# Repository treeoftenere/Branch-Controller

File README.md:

# Branch-Controller

The branch controllers are running on STM32 Bluepill boards with a wiznet w5500 based ethernet module.

The branch controller depends on the following:
1. Arduino support for STM32F1  ** master? **
2. FastLED with support for STM32F1  ** Currently uses Tenere Branch **
3. Ethernet library, based on the teensy implementation with faster settings  ** master? **

## Arduino settings:
Board:  Generic STM32F103C
Upload Method:  JLink

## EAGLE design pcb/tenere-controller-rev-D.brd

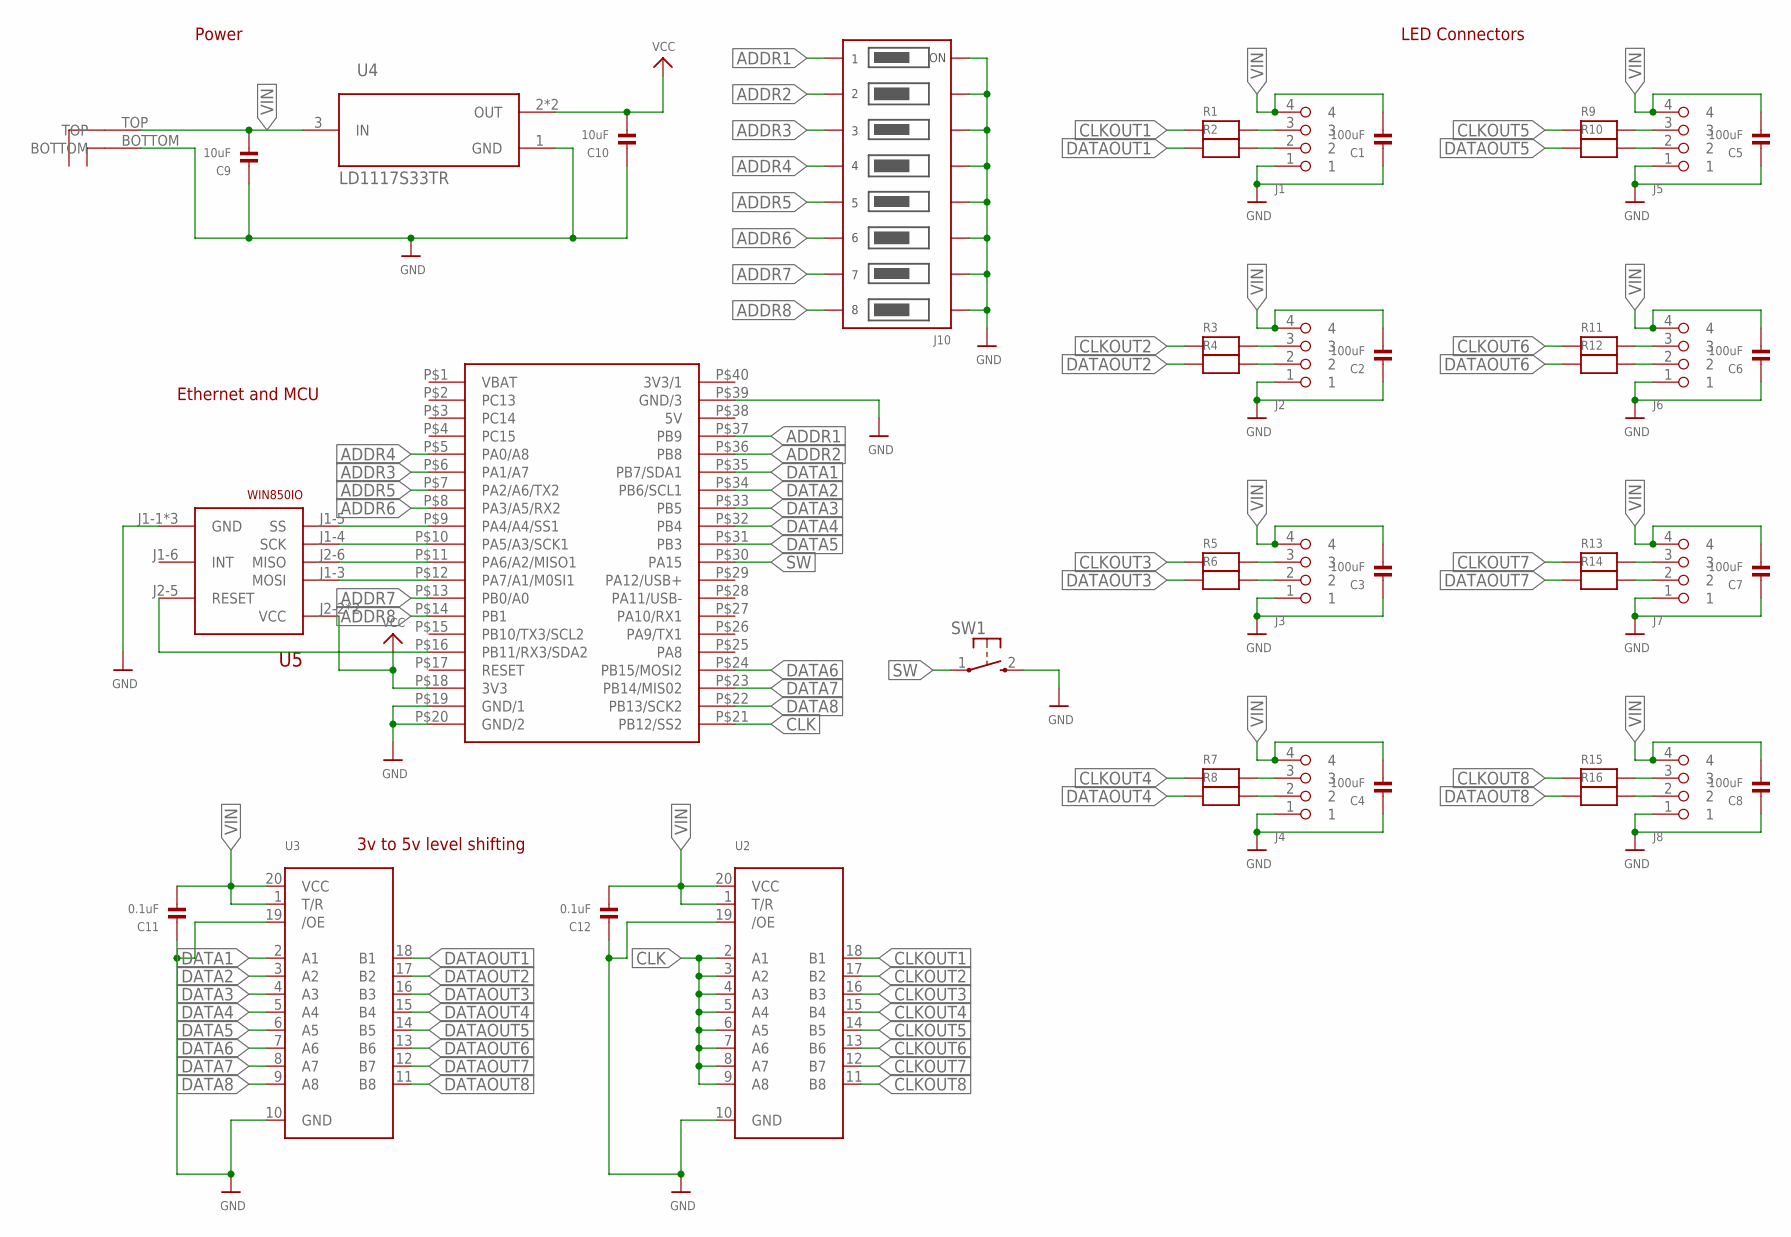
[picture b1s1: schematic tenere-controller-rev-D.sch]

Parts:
C1, C2, C3, C4, C5, C6, C7, C8: 100uF; 1206
C9, C10: 10uF; 0603
C11, C12: 0.1uF; 0603
J1, J2, J3, J4, J5, J6, J7, J8: MICROFIT3; 43650-0400
J9: POWERPOLE-2V; POWERPOLE_STACKED
J10: DIP-SWITCH-8PIN; BPA08B
R1, R2, R3, R4, R5, R6, R7, R8, R9, R10, R11, R12, R13, R14, R15, R16: RESISTOR0603; 0603
SW1: TACTILE-SWITCH-1825027; 1825027
U1: BLUEPILL; 40-DIP-BLUE-PIL
U2, U3: 74LCX245; TSSOP20
U4: LD1117S33TR; LD1117S33TR_SOT230P700X180-4N
U5: WIN850IO; WIZ850IO

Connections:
ADDR1: J10.1' (1B), U1.P$37 (PB9)
ADDR2: J10.2' (2B), U1.P$36 (PB8)
ADDR3: J10.3' (3B), U1.P$6 (PA1/A7)
ADDR4: J10.4' (4B), U1.P$5 (PA0/A8)
ADDR5: J10.5' (5B), U1.P$7 (PA2/A6/TX2)
ADDR6: J10.6' (6B), U1.P$8 (PA3/A5/RX2)
ADDR7: J10.7' (7B), U1.P$13 (PB0/A0)
ADDR8: J10.8' (8B), U1.P$14 (PB1)
CLK: U1.P$21 (PB12/SS2), U2.2 (A1), U2.3 (A2), U2.4 (A3), U2.5 (A4), U2.6 (A5), U2.7 (A6), U2.8 (A7), U2.9 (A8)
CLKOUT1: R1.1, U2.18 (B1)
CLKOUT2: R3.1, U2.17 (B2)
CLKOUT3: R5.1, U2.16 (B3)
CLKOUT4: R7.1, U2.15 (B4)
CLKOUT5: R9.1, U2.14 (B5)
CLKOUT6: R11.1, U2.13 (B6)
CLKOUT7: R13.1, U2.12 (B7)
CLKOUT8: R15.1, U2.11 (B8)
DATA1: U1.P$35 (PB7/SDA1), U3.2 (A1)
DATA2: U1.P$34 (PB6/SCL1), U3.3 (A2)
DATA3: U1.P$33 (PB5), U3.4 (A3)
DATA4: U1.P$32 (PB4), U3.5 (A4)
DATA5: U1.P$31 (PB3), U3.6 (A5)
DATA6: U1.P$24 (PB15/MOSI2), U3.7 (A6)
DATA7: U1.P$23 (PB14/MIS02), U3.8 (A7)
DATA8: U1.P$22 (PB13/SCK2), U3.9 (A8)
DATAOUT1: R2.1, U3.18 (B1)
DATAOUT2: R4.1, U3.17 (B2)
DATAOUT3: R6.1, U3.16 (B3)
DATAOUT4: R8.1, U3.15 (B4)
DATAOUT5: R10.1, U3.14 (B5)
DATAOUT6: R12.1, U3.13 (B6)
DATAOUT7: R14.1, U3.12 (B7)
DATAOUT8: R16.1, U3.11 (B8)
GND: C1.1, C2.1, C3.1, C4.1, C5.1, C6.1, C7.1, C8.1, C9.1, C10.1, C11.1, C12.1, J1.1, J2.1, J3.1, J4.1, J5.1, J6.1, J7.1, J8.1, J9.BOTTOM, J10.1 (1A), J10.2 (2A), J10.3 (3A), J10.4 (4A), J10.5 (5A), J10.6 (6A), J10.7 (7A), J10.8 (8A), SW1.2 (3), U1.P$19 (GND/1), U1.P$20 (GND/2), U1.P$39 (GND/3), U2.10 (GND), U2.19 (/OE), U3.10 (GND), U3.19 (/OE), U4.1 (GND), U5.J1-1 (GND), U5.J1-2 (GND), U5.J2-1 (GND)
unnamed: U1.P$9 (PA4/A4/SS1), U5.J1-5 (SS)
unnamed: U1.P$10 (PA5/A3/SCK1), U5.J1-4 (SCK)
unnamed: U1.P$11 (PA6/A2/MISO1), U5.J2-6 (MISO)
unnamed: U1.P$12 (PA7/A1/M0SI1), U5.J1-3 (MOSI)
unnamed: J1.3, R1.2
unnamed: J1.2, R2.2
unnamed: J2.3, R3.2
unnamed: J2.2, R4.2
unnamed: J3.3, R5.2
unnamed: J3.2, R6.2
unnamed: J4.3, R7.2
unnamed: J4.2, R8.2
unnamed: J5.3, R9.2
unnamed: J5.2, R10.2
unnamed: J6.3, R11.2
unnamed: J6.2, R12.2
unnamed: J7.3, R13.2
unnamed: J7.2, R14.2
unnamed: J8.3, R15.2
unnamed: J8.2, R16.2
unnamed: U1.P$16 (PB11/RX3/SDA2), U5.J2-5 (RESET)
SW: SW1.1, U1.P$30 (PA15)
VCC: C10.2, U1.P$18 (3V3), U4.2 (OUT), U4.4 (OUT), U5.J2-2 (VCC), U5.J2-3 (VCC)
VIN: C1.2, C2.2, C3.2, C4.2, C5.2, C6.2, C7.2, C8.2, C9.2, C11.2, C12.2, J1.4, J2.4, J3.4, J4.4, J5.4, J6.4, J7.4, J8.4, J9.TOP, U2.1 (T/R), U2.20 (VCC), U3.1 (T/R), U3.20 (VCC), U4.3 (IN)

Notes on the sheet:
LED Connectors
Power
Ethernet and MCU
3v to 5v level shifting

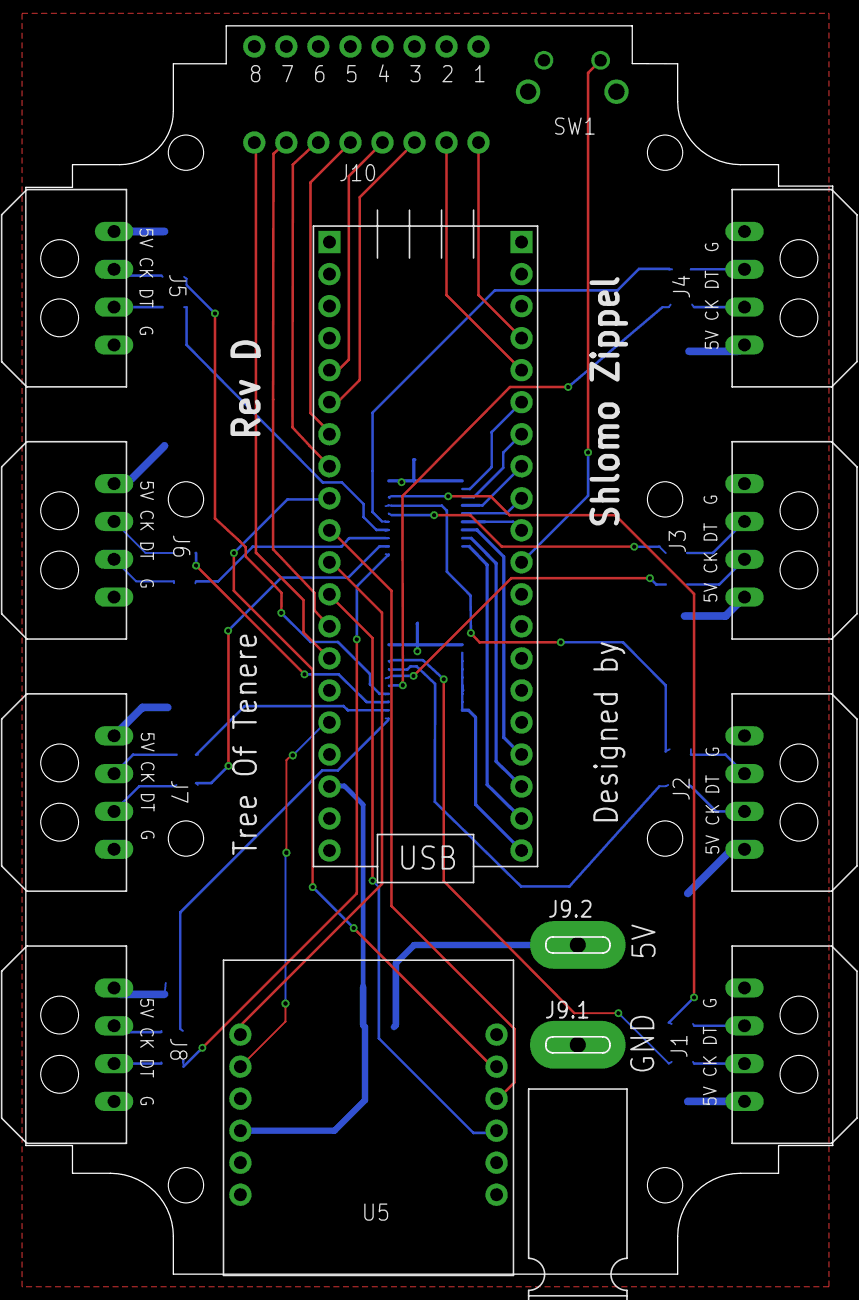
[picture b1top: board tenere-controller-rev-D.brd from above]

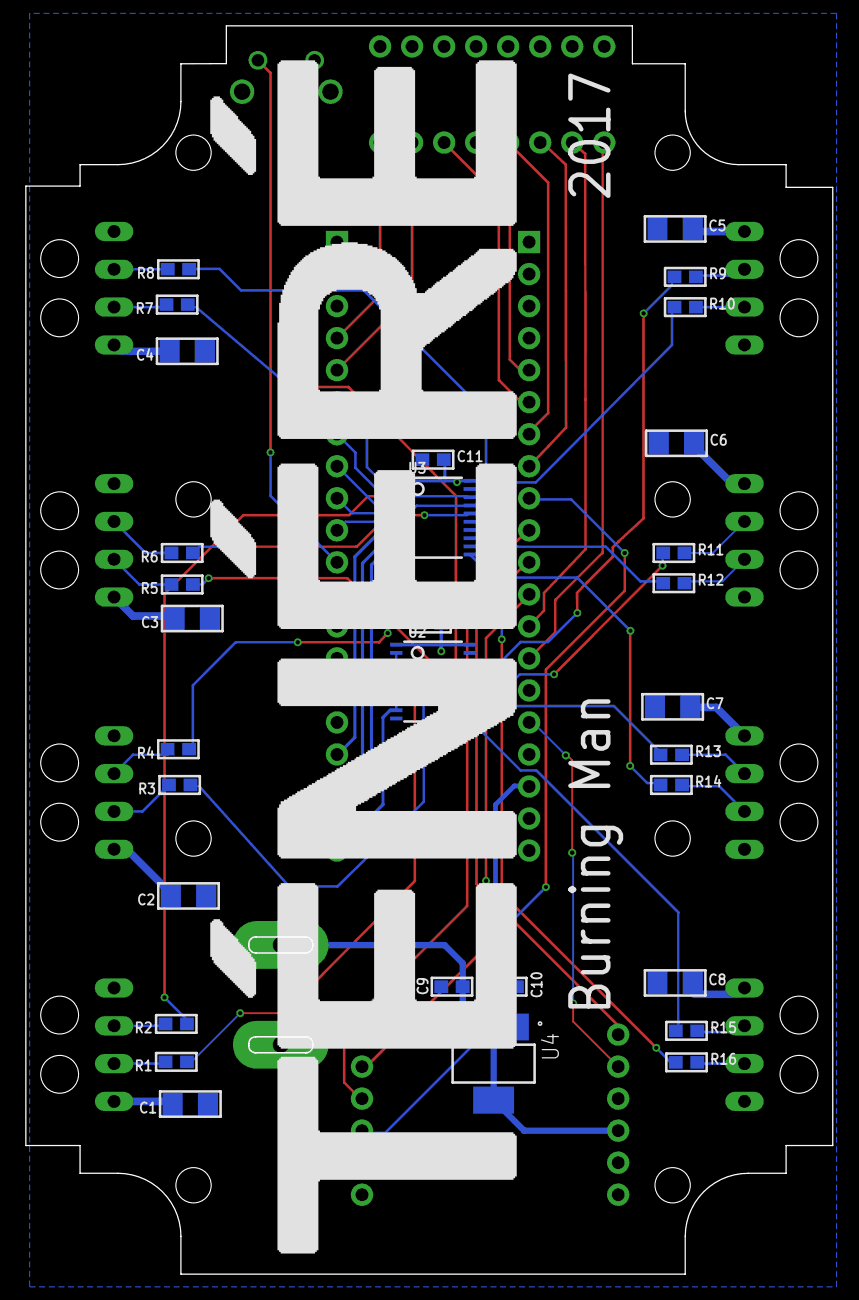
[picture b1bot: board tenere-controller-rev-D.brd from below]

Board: 2 copper layers, 64.0 x 99.0 mm, 45 parts (31 on the bottom side), 58 nets.

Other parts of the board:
U$15: 105*65

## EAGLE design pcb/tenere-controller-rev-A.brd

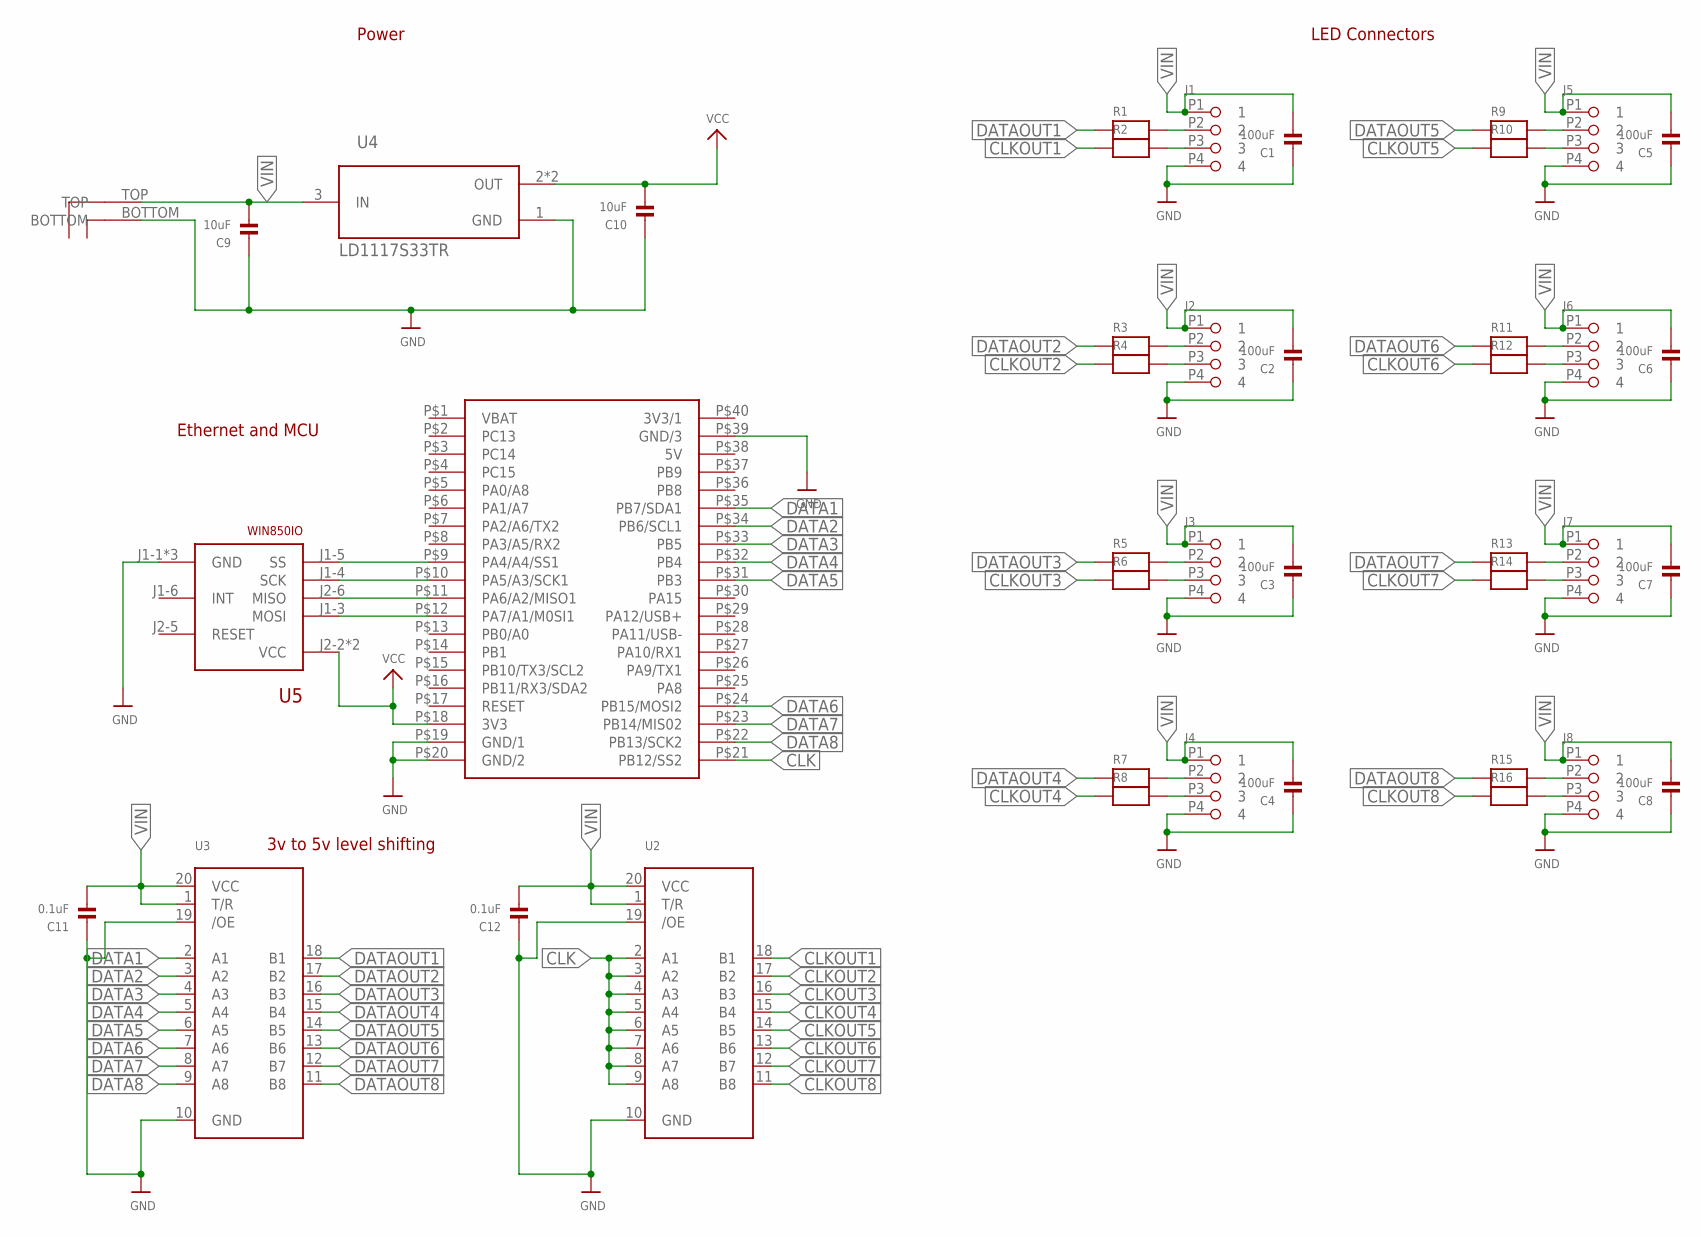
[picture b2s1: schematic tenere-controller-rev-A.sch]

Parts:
C1, C2, C3, C4, C5, C6, C7, C8: 100uF; 1206
C9, C10: 10uF; 0603
C11, C12: 0.1uF; 0603
J1, J2, J3, J4, J5, J6, J7, J8: JST-XH-4P-SODE; JST-XH-BS4P
J9: POWERPOLE-2V; POWERPOLE_STACKED
R1, R2, R3, R4, R5, R6, R7, R8, R9, R10, R11, R12, R13, R14, R15, R16: RESISTOR0603; 0603
U1: BLUEPILL; 40-DIP-BLUE-PIL
U2, U3: 74LCX245; TSSOP20
U4: LD1117S33TR; LD1117S33TR_SOT230P700X180-4N
U5: WIN850IO; WIZ850IO

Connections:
CLK: U1.P$21 (PB12/SS2), U2.2 (A1), U2.3 (A2), U2.4 (A3), U2.5 (A4), U2.6 (A5), U2.7 (A6), U2.8 (A7), U2.9 (A8)
CLKOUT1: R2.1, U2.18 (B1)
CLKOUT2: R4.1, U2.17 (B2)
CLKOUT3: R6.1, U2.16 (B3)
CLKOUT4: R8.1, U2.15 (B4)
CLKOUT5: R10.1, U2.14 (B5)
CLKOUT6: R12.1, U2.13 (B6)
CLKOUT7: R14.1, U2.12 (B7)
CLKOUT8: R16.1, U2.11 (B8)
DATA1: U1.P$35 (PB7/SDA1), U3.2 (A1)
DATA2: U1.P$34 (PB6/SCL1), U3.3 (A2)
DATA3: U1.P$33 (PB5), U3.4 (A3)
DATA4: U1.P$32 (PB4), U3.5 (A4)
DATA5: U1.P$31 (PB3), U3.6 (A5)
DATA6: U1.P$24 (PB15/MOSI2), U3.7 (A6)
DATA7: U1.P$23 (PB14/MIS02), U3.8 (A7)
DATA8: U1.P$22 (PB13/SCK2), U3.9 (A8)
DATAOUT1: R1.1, U3.18 (B1)
DATAOUT2: R3.1, U3.17 (B2)
DATAOUT3: R5.1, U3.16 (B3)
DATAOUT4: R7.1, U3.15 (B4)
DATAOUT5: R9.1, U3.14 (B5)
DATAOUT6: R11.1, U3.13 (B6)
DATAOUT7: R13.1, U3.12 (B7)
DATAOUT8: R15.1, U3.11 (B8)
GND: C1.1, C2.1, C3.1, C4.1, C5.1, C6.1, C7.1, C8.1, C9.1, C10.1, C11.1, C12.1, J1.P4 (4), J2.P4 (4), J3.P4 (4), J4.P4 (4), J5.P4 (4), J6.P4 (4), J7.P4 (4), J8.P4 (4), J9.BOTTOM, U1.P$19 (GND/1), U1.P$20 (GND/2), U1.P$39 (GND/3), U2.10 (GND), U2.19 (/OE), U3.10 (GND), U3.19 (/OE), U4.1 (GND), U5.J1-1 (GND), U5.J1-2 (GND), U5.J2-1 (GND)
unnamed: U1.P$9 (PA4/A4/SS1), U5.J1-5 (SS)
unnamed: U1.P$10 (PA5/A3/SCK1), U5.J1-4 (SCK)
unnamed: U1.P$11 (PA6/A2/MISO1), U5.J2-6 (MISO)
unnamed: U1.P$12 (PA7/A1/M0SI1), U5.J1-3 (MOSI)
unnamed: J1.P2 (2), R1.2
unnamed: J1.P3 (3), R2.2
unnamed: J2.P2 (2), R3.2
unnamed: J2.P3 (3), R4.2
unnamed: J3.P2 (2), R5.2
unnamed: J3.P3 (3), R6.2
unnamed: J4.P2 (2), R7.2
unnamed: J4.P3 (3), R8.2
unnamed: J5.P2 (2), R9.2
unnamed: J5.P3 (3), R10.2
unnamed: J6.P2 (2), R11.2
unnamed: J6.P3 (3), R12.2
unnamed: J7.P2 (2), R13.2
unnamed: J7.P3 (3), R14.2
unnamed: J8.P2 (2), R15.2
unnamed: J8.P3 (3), R16.2
VCC: C10.2, U1.P$18 (3V3), U4.2 (OUT), U4.4 (OUT), U5.J2-2 (VCC), U5.J2-3 (VCC)
VIN: C1.2, C2.2, C3.2, C4.2, C5.2, C6.2, C7.2, C8.2, C9.2, C11.2, C12.2, J1.P1 (1), J2.P1 (1), J3.P1 (1), J4.P1 (1), J5.P1 (1), J6.P1 (1), J7.P1 (1), J8.P1 (1), J9.TOP, U2.1 (T/R), U2.20 (VCC), U3.1 (T/R), U3.20 (VCC), U4.3 (IN)

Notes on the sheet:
LED Connectors
Power
Ethernet and MCU
3v to 5v level shifting

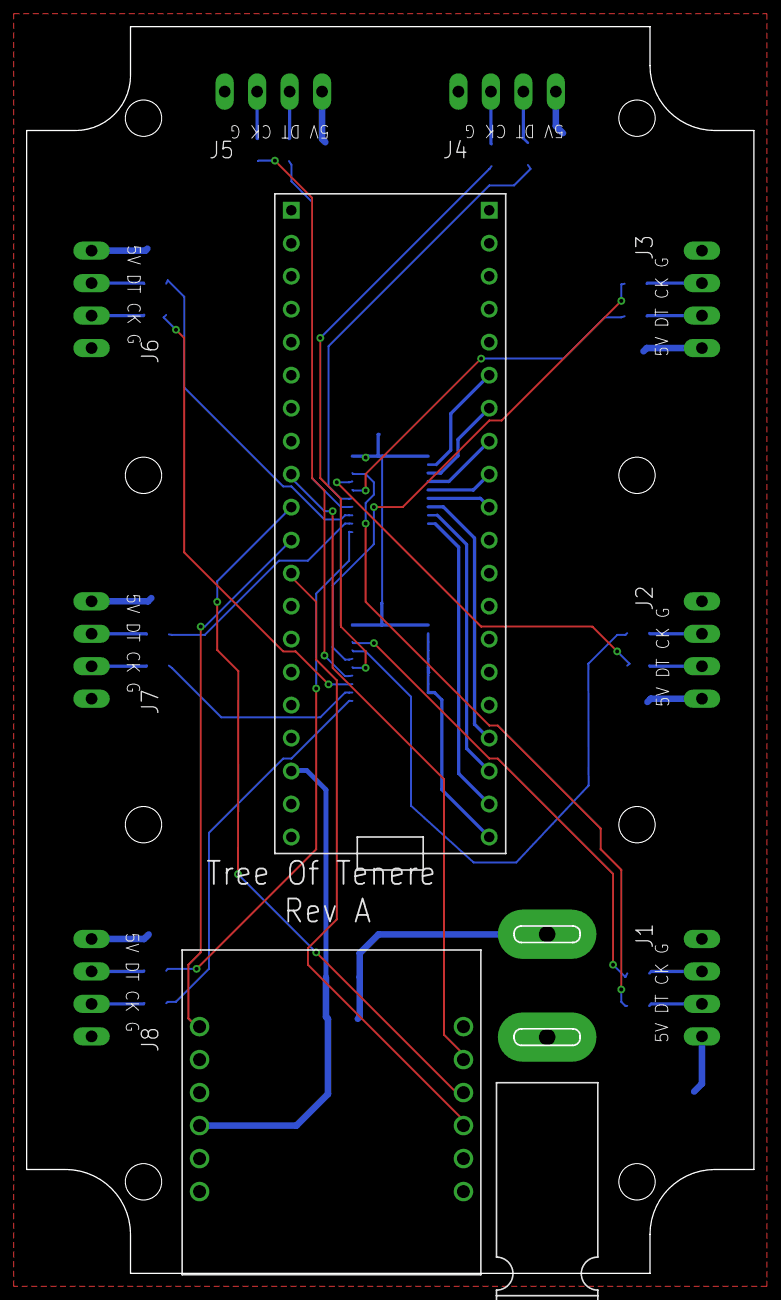
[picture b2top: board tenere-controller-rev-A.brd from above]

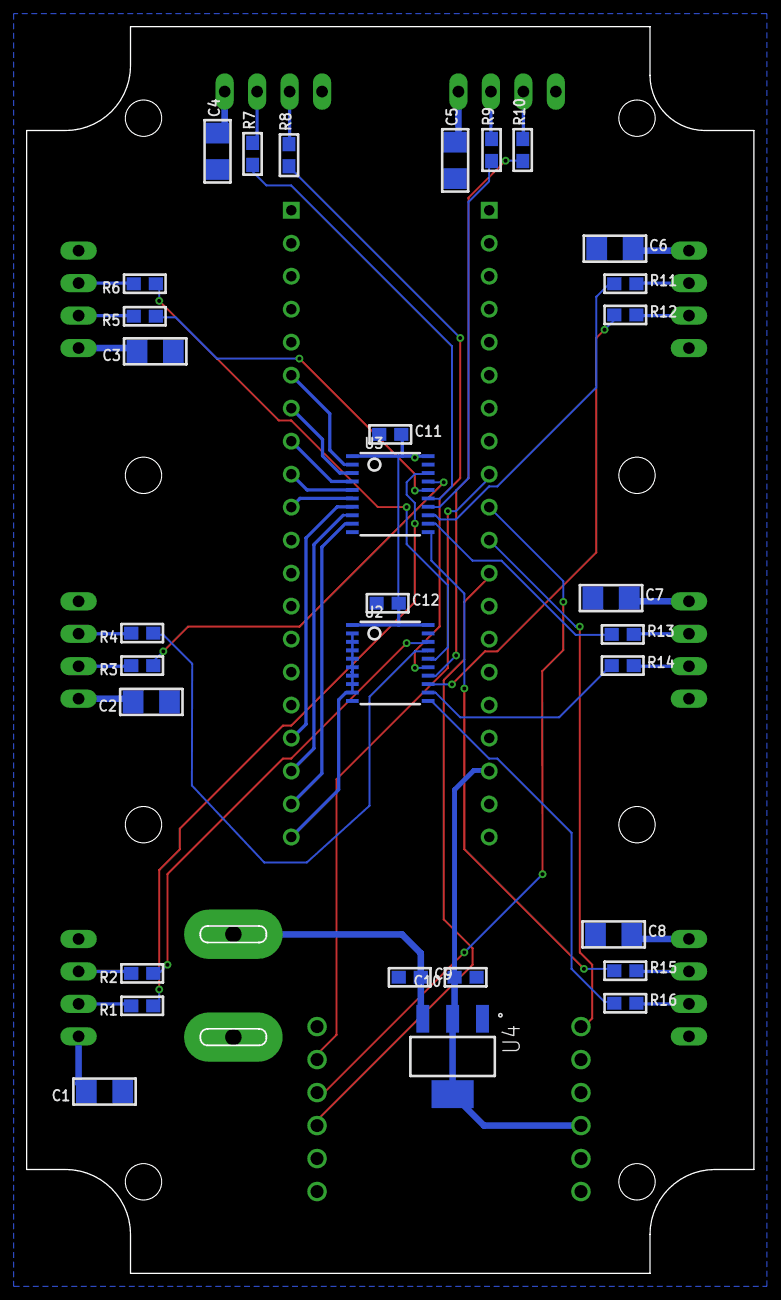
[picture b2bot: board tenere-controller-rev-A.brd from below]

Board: 2 copper layers, 56.0 x 96.0 mm, 43 parts (31 on the bottom side), 48 nets.

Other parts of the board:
U$15: 105*65

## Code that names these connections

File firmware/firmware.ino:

#include <SPI.h>
#include <Ethernet.h>
#include <FastLED.h>
#include <EEPROM.h>
#include "button.h"

#define LEDS_PER_CHANNEL    105
#define NUM_CHANNELS        8
#define NUM_LEDS            (NUM_CHANNELS * LEDS_PER_CHANNEL)
#define COLOR_ORDER         BGR
#define SPI_RATE            DATA_RATE_MHZ(4)
#define UDP_RX_BUFFER_SIZE  8192
#define UDP_PORT_NUMBER     1337

#define PARALLEL_OUTPUT
#define PLAYA_MODE

//-------------------------------------------------------------------------------------------
// Pin mappings
//-------------------------------------------------------------------------------------------

//#define REVB
#define REVC

#ifdef REVB
uint8_t dip_switch_pins[] = {PA0, PA1, PA2, PA3, PB0};
#define SWITCH_PIN  PB1
#endif 

#ifdef REVC
uint8_t dip_switch_pins[] = {PB9, PB8, PA1, PA0, PA2, PA3, PB0, PB1};
#define SWITCH_PIN  PA15
#endif

#define FPS_PIN         PA0
#define CLOCK_PIN       PB12
#define ETHERNET_CS_PIN PA4
#define INDICATOR_PIN   PC13

#define ARRAY_SIZE(A) (sizeof(A) / sizeof((A)[0]))

CRGB leds[NUM_CHANNELS][LEDS_PER_CHANNEL];

typedef struct _opc_header_t {
  uint8_t channel;
  uint8_t command;
  uint8_t datalen_h;
  uint8_t datalen_l;
  uint8_t data[];
} opc_header_t;

EthernetUDP Udp;
char packet_buffer[UDP_RX_BUFFER_SIZE]; 

FastPin<FPS_PIN> fps;

Button sw(SWITCH_PIN);

uint32_t last_packet_time = 0;
uint8_t brightness = 0;

//-------------------------------------------------------------------------------------------
// IP & Mac address
//-------------------------------------------------------------------------------------------

// this default mac seems to work well as a template, lets just replace a single
// byte based on controller address
byte mac[] = {
  0xDE, 0xAD, 0xBE, 0xEF, 0xFE, 0xED
};

uint8_t get_address() {
    uint8_t result = 0;
    for (int i = 0; i < ARRAY_SIZE(dip_switch_pins); i++) {
        result = result | !digitalRead(dip_switch_pins[i]) << i;
    }
    return result;
}


//-------------------------------------------------------------------------------------------
// Test patterns
//-------------------------------------------------------------------------------------------

void network() {
  // clear the buffer if we didn't receive a packet for a while
  int32_t delta = millis() - last_packet_time - 10000;
  if (delta > 10000) {
    brightness = 0;
  } else if (delta > 0) {
    brightness = map(delta, 0, 10000, 255, 0);
  } else {
    brightness = qadd8(brightness, 5);
  }

  FastLED.setBrightness(brightness);
}

void rainbow() {
    static uint8_t hue=0;
    fill_rainbow((CRGB*)leds, NUM_LEDS, ++hue, 10);  
}

void fullwhite() {
    fill_solid((CRGB*)leds, NUM_LEDS, CRGB::White);  
}

typedef void (*SimplePatternList[])();
uint8_t g_current_pattern = 0;

SimplePatternList patterns = {
  network,
  rainbow,
  //fullwhite,
};

void render() {
  (patterns)[g_current_pattern]();
  FastLED.delay(1000/120);
}

void next_pattern()
{
  g_current_pattern = (g_current_pattern + 1) % ARRAY_SIZE( patterns);
  fill_solid((CRGB*)leds, NUM_LEDS, CRGB::Black);
  FastLED.setBrightness(255);
}


//-------------------------------------------------------------------------------------------
// Network code
//-------------------------------------------------------------------------------------------

bool got_a_packet = false;

void network_connect() {
  Ethernet.init(ETHERNET_CS_PIN);
  Ethernet.softReset();

  // attempt to read stored address first
  uint8_t addr;
  addr = EEPROM.read(0);
  if (255 == addr) {
      addr = get_address();
  }
  
  mac[2] = addr;
  IPAddress ip_addr(192, 168, 1, addr);
  Ethernet.begin(mac, ip_addr);
  Udp.begin(UDP_PORT_NUMBER);
}

void network_poll() {
  int packet_size = Udp.parsePacket();
  static int remaining = 0;
  if (packet_size > 0) {
    got_a_packet = true;
    last_packet_time = millis();
    FastLED.setBrightness(255);

    // force us into network mode if we receive a packet
    g_current_pattern = 0;
    
    
    remaining += Udp.read(packet_buffer+remaining,UDP_RX_BUFFER_SIZE);
    opc_header_t * header = (opc_header_t *)packet_buffer;
    while (remaining > 4) {
      fps.toggle();
      uint16_t data_size = header->datalen_h << 8 | header->datalen_l;
      uint16_t offset = (int)header->channel * LEDS_PER_CHANNEL * 3;
      memcpy8((uint8_t *) leds + offset, header->data, min(data_size, remaining-4));
      remaining -= (data_size + 4);
      header = (opc_header_t *) (packet_buffer+data_size+4);

      // intermediate render if we have multiple frames in this packet
      if (remaining > 4) {
        render();
      }
    }
  }
}

//-------------------------------------------------------------------------------------------
// Button handlers
//-------------------------------------------------------------------------------------------

void button_press() {
  // Only switch modes on playa if we don't have network activity
  #ifdef PLAYA_MODE
  if (!got_a_packet)
  #endif
    next_pattern();
}

void button_hold() {
  EEPROM.write(0, get_address());  
  network_connect();

  digitalWrite(INDICATOR_PIN, LOW);
  delay(250);
  digitalWrite(INDICATOR_PIN, HIGH);
  delay(250);
  digitalWrite(INDICATOR_PIN, LOW);
  delay(250);
  digitalWrite(INDICATOR_PIN, HIGH);
}

void setup() {
  #ifdef REVB
    #ifdef PARALLEL_OUTPUT
      FastLED.addLeds<TENERE_REVB, CLOCK_PIN, COLOR_ORDER, SPI_RATE>(leds, LEDS_PER_CHANNEL);
    #else
      FastLED.addLeds<APA102, PB13, CLOCK_PIN, COLOR_ORDER, SPI_RATE>(leds[0],LEDS_PER_CHANNEL);
      FastLED.addLeds<APA102, PB14, CLOCK_PIN, COLOR_ORDER, SPI_RATE>(leds[1],LEDS_PER_CHANNEL);
      FastLED.addLeds<APA102, PB15, CLOCK_PIN, COLOR_ORDER, SPI_RATE>(leds[2],LEDS_PER_CHANNEL);
      FastLED.addLeds<APA102, PB5, CLOCK_PIN, COLOR_ORDER, SPI_RATE>(leds[3],LEDS_PER_CHANNEL);
      FastLED.addLeds<APA102, PB6, CLOCK_PIN, COLOR_ORDER, SPI_RATE>(leds[4],LEDS_PER_CHANNEL);
      FastLED.addLeds<APA102, PB7, CLOCK_PIN, COLOR_ORDER, SPI_RATE>(leds[5],LEDS_PER_CHANNEL);
      FastLED.addLeds<APA102, PB8, CLOCK_PIN, COLOR_ORDER, SPI_RATE>(leds[6],LEDS_PER_CHANNEL);
      FastLED.addLeds<APA102, PB9, CLOCK_PIN, COLOR_ORDER, SPI_RATE>(leds[7],LEDS_PER_CHANNEL);
    #endif
  #endif

  #ifdef REVC
    #ifdef PARALLEL_OUTPUT
      FastLED.addLeds<TENERE_REVC, CLOCK_PIN, COLOR_ORDER, SPI_RATE>((CRGB *)leds, LEDS_PER_CHANNEL);
    #else
      FastLED.addLeds<APA102, PB7, CLOCK_PIN, COLOR_ORDER, SPI_RATE>(leds[0],LEDS_PER_CHANNEL);
      FastLED.addLeds<APA102, PB6, CLOCK_PIN, COLOR_ORDER, SPI_RATE>(leds[1],LEDS_PER_CHANNEL);
      FastLED.addLeds<APA102, PB5, CLOCK_PIN, COLOR_ORDER, SPI_RATE>(leds[2],LEDS_PER_CHANNEL);
      FastLED.addLeds<APA102, PB4, CLOCK_PIN, COLOR_ORDER, SPI_RATE>(leds[3],LEDS_PER_CHANNEL);
      FastLED.addLeds<APA102, PB3, CLOCK_PIN, COLOR_ORDER, SPI_RATE>(leds[4],LEDS_PER_CHANNEL);
      FastLED.addLeds<APA102, PB15, CLOCK_PIN, COLOR_ORDER, SPI_RATE>(leds[5],LEDS_PER_CHANNEL);
      FastLED.addLeds<APA102, PB14, CLOCK_PIN, COLOR_ORDER, SPI_RATE>(leds[6],LEDS_PER_CHANNEL);
      FastLED.addLeds<APA102, PB13, CLOCK_PIN, COLOR_ORDER, SPI_RATE>(leds[7],LEDS_PER_CHANNEL);
    #endif
  #endif
  
  FastLED.setBrightness(255);
  SPI.begin();

  // debug pin
  fps.setOutput();

  // ip address dip switch
   for (int i = 0; i < ARRAY_SIZE(dip_switch_pins); i++) {
       pinMode(dip_switch_pins[i], INPUT_PULLUP);
   }

   // indicator LED
   pinMode(INDICATOR_PIN, OUTPUT);
   digitalWrite(INDICATOR_PIN, HIGH);

   // wait a bit before connecting to ensure the switches are powered on
   delay(3000);
   network_connect();
}


void loop() {
  sw.poll(button_press, button_hold);

  network_poll();
  
  render();  
}

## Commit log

2017-06-11 Added initial pcb, mechanical, firmware
2017-06-15 controller rev b pcb
2017-06-15 Minor change to one of the connectors
2017-06-15 Silkscreen fixes
2017-06-15 Minor fixes for oshpark drc
2017-06-25 Rev C
2017-06-30 changes to show rainbow on rev B
2017-08-01 Up to date test code
2017-08-06 unique ip / mac should work now
2017-08-06 Parallel output
2017-08-09 latest changes
2017-08-10 Added flasher script. Submodules here too.
2017-08-10 Dependency version info. Arduino settings.
2017-08-12 playafied
2017-08-14 Playa binary and flash script
2018-11-01 Initial processing template based on fadecandy processing code
2018-11-11 Updated OPC code to support multiple strips
2018-11-13 fixed pixel locations
2019-01-17 Added Rev D PCB
2019-01-19 Added BOM file for Rev D

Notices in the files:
parts and their libraries:
microbuilder: This work is placed in the public domain, and may be freely used for commercial and non-commercial work with the following conditions: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
